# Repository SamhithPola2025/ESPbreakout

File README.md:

# ESPbreakout
## Overview
ESPbreakout is a breakout board for the popular ESP32-s3  chip that includes many breakout pins, compatible with any other ESP32 setup (for the most part), and has programming via USB 2.0.
This board uses the ESP32-S3 SOC, which means that it does not use any of the modules that espressif has already made, and just the bare ESP32-S3 chip.
This board includes pins for progamming, a USB-C port (for programming & power), a screw terminal to convenient wire up a Lithium battery to (3.7v). And you can also utilize the PSRAM that I added externally onto the board. The board includes comprehensive labels for buttons and pins, for ease of use. The cost and materials used to manafacture/make this board are in the BOM.csv file.

## Intent behind making this board:
I made this board to showcase what I already know, and to learn a lot of new things (I can say that this one was accomplished). I also made this board to act as a substitute for the ESP32-S3 devboard that exists, and of course it wont be better than the board made by the actual company, Espressif, but it will be pretty decent and working!

## Pictures

(Pictures of the built version will be added once I get all the components and solder what needs to be soldered, for the most part this is PCBA though.)

| Reference | Quantity | Part                                                   | Unit Price | Extended Price |
| --------- | -------- | ------------------------------------------------------ | ---------- | -------------- |
| PCBA      | 1        | PCBA Estimate                                          | $52.55     | $52.55         |
| B1        | 1        | TinyCircuits BATTERY LITH-ION 3.7V 1AH                 | $9.95      | $9.95          |
| C1        | 1        | Pololu 2PIN F JST PH-STYLE CABLE 12CM                  | $1.47      | $1.47          |
| J1        | 3        | Sullins Connector Solutions CONN HDR 4POS 0.1 GOLD PCB | $0.38      | $1.14          |
| J2        | 1        | Phoenix Contact TERM BLK 2POS SIDE ENTRY 5MM PCB       | $0.78      | $0.78          |
| **Total** |          |                                                        |            | **$71.89**     |

Note: $6.00 of buffer is added for shipping or tariff changes. Any unused buffer will be returned.

## Cart screenshots

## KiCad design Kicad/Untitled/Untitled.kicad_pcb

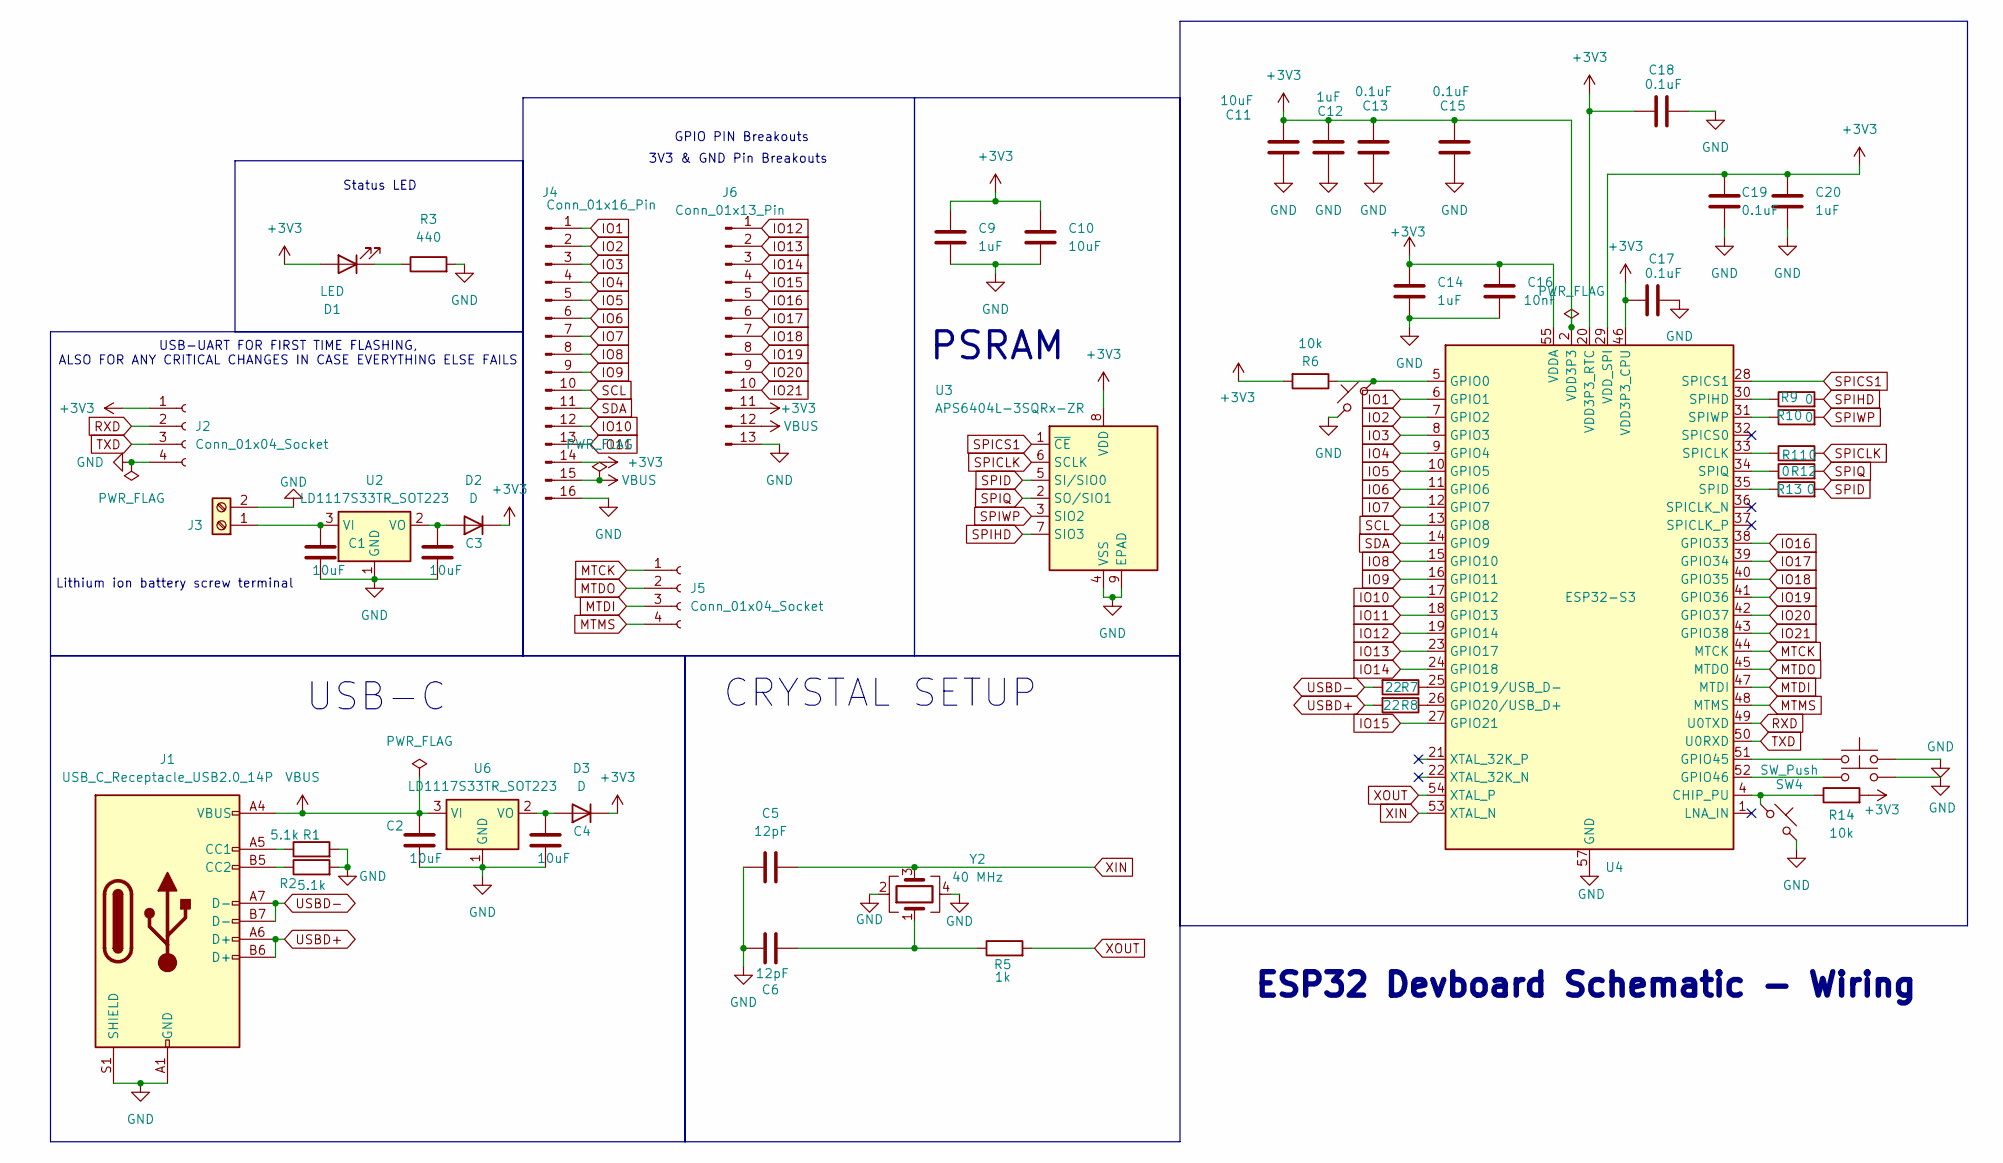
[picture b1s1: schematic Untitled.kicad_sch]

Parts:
C1, C2, C3, C4, C10, C11: 10uF; C_0402_1005Metric
C5, C6: 12pF; C_0402_1005Metric
C9, C12, C14, C20: 1uF; C_0402_1005Metric
C13, C15, C17, C18, C19: 0.1uF; C_0402_1005Metric
C16: 10nF; C_0402_1005Metric
D1: LED; LED_WS2812B-Mini_PLCC4_3.5x3.5mm
D2, D3: D; D_0402_1005Metric
J1: USB_C_Receptacle_USB2.0_14P; HRO_TYPE-C-31-M-12
J2, J5: Conn_01x04_Socket; PinSocket_1x04_P2.54mm_Horizontal
J3: Screw_Terminal_01x02; TerminalBlock_Phoenix_MKDS-1,5-2-5.08_1x02_P5.08mm_Horizont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
J4: Conn_01x16_Pin; PinHeader_1x16_P2.54mm_Vertical
J6: Conn_01x13_Pin; PinHeader_1x13_P2.54mm_Vertical
R1, R2: 5.1k; R_0402_1005Metric
R3: 440; R_0402_1005Metric
R5: 1k; R_0402_1005Metric
R6, R14: 10k; R_0402_1005Metric
R7, R8: 22; R_0402_1005Metric
R9, R10, R11, R12, R13: 0; R_0201_0603Metric
SW1, SW2: SW_Push_45deg; SW_SPST_B3U-1000P
SW3, SW4: SW_Push; SW_SPST_B3U-1000P
U2, U6: LD1117S33TR_SOT223; SOT-223-3_TabPin2
U3: APS6404L-3SQRx-ZR; Winbond_USON-8-1EP_3x2mm_P0.5mm_EP0.2x1.6mm
U4: ESP32-S3; QFN-56-1EP_7x7mm_P0.4mm_EP4x4mm
Y2: 40 MHz; OSC_CX2016DB40000D0FLJCC

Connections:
+3V3: C9.1, C10.1, C11.2, C12.2, C13.2, C14.1, C15.2, C16.1, C17.1, C18.1, C19.1, C20.1, D1.2 (A), D2.1 (K), D3.1 (K), J2.1, J4.14, J6.11, R6.2, R14.2, U3.8 (VDD), U4.2 (VDD3P3), U4.3 (VDD3P3), U4.20 (VDD3P3_RTC), U4.29 (VDD_SPI), U4.46 (VDD3P3_CPU), U4.55 (VDDA), U4.56 (VDDA)
GND: C1.2, C2.2, C3.2, C4.2, C5.1, C6.1, C9.2, C10.2, C11.1, C12.1, C13.1, C14.2, C15.1, C16.2, C17.2, C18.2, C19.2, C20.2, J1.A1 (GND), J1.A12 (GND), J1.B1 (GND), J1.B12 (GND), J1.S1 (SHIELD), J2.4, J3.2, J4.16, J6.13, R1.2, R2.2, R3.2, SW1.1, SW2.2, SW3.2, SW4.2, U2.1 (GND), U3.4 (VSS), U3.9 (EPAD), U4.57 (GND), U6.1 (GND), Y2.2, Y2.4; also elsewhere on the board
IO1: J4.1, U4.6 (GPIO1)
IO2: J4.2, U4.7 (GPIO2)
IO3: J4.3, U4.8 (GPIO3)
IO4: J4.4, U4.9 (GPIO4)
IO5: J4.5, U4.10 (GPIO5)
IO6: J4.6, U4.11 (GPIO6)
IO7: J4.7, U4.12 (GPIO7)
IO8: J4.8, U4.15 (GPIO10)
IO9: J4.9, U4.16 (GPIO11)
IO10: J4.12, U4.17 (GPIO12)
IO11: J4.13, U4.18 (GPIO13)
IO12: J6.1, U4.19 (GPIO14)
IO13: J6.2, U4.23 (GPIO17)
IO14: J6.3, U4.24 (GPIO18)
IO15: J6.4, U4.27 (GPIO21)
IO16: J6.5, U4.38 (GPIO33)
IO17: J6.6, U4.39 (GPIO34)
IO18: J6.7, U4.40 (GPIO35)
IO19: J6.8, U4.41 (GPIO36)
IO20: J6.9, U4.42 (GPIO37)
IO21: J6.10, U4.43 (GPIO38)
MTCK: J5.1, U4.44 (MTCK)
MTDI: J5.3, U4.47 (MTDI)
MTDO: J5.2, U4.45 (MTDO)
MTMS: J5.4, U4.48 (MTMS)
unnamed: C6.2, R5.1, Y2.1
unnamed: D1.1 (K), R3.1
unnamed 29: C3.1, D2.2 (A), U2.2 (VO); also elsewhere on the board
unnamed: C4.1, D3.2 (A), U6.2 (VO)
unnamed: J1.A5 (CC1), R1.1
unnamed: J1.B5 (CC2), R2.1
unnamed 33: C1.1, J3.1, U2.3 (VI); also elsewhere on the board
unnamed: R14.1, SW2.1, U4.4 (CHIP_PU)
unnamed: R6.1, SW1.2, U4.5 (GPIO0)
unnamed: R7.1, U4.25 (GPIO19/USB_D-)
unnamed: R8.1, U4.26 (GPIO20/USB_D+)
unnamed: SW3.1, U4.51 (GPIO45)
unnamed: SW4.1, U4.52 (GPIO46)
unnamed: R11.1, U4.33 (SPICLK)
unnamed: R13.1, U4.35 (SPID)
unnamed: R9.1, U4.30 (SPIHD)
unnamed: R12.1, U4.34 (SPIQ)
unnamed: R10.1, U4.31 (SPIWP)
RXD: J2.2, U4.49 (U0TXD)
SCL: J4.10, U4.13 (GPIO8)
SDA: J4.11, U4.14 (GPIO9)
SPICLK: R11.2, U3.6 (SCLK)
SPICS1: U3.1 (~CE), U4.28 (SPICS1)
SPID: R13.2, U3.5 (SI/SIO0)
SPIHD: R9.2, U3.7 (SIO3)
SPIQ: R12.2, U3.2 (SO/SIO1)
SPIWP: R10.2, U3.3 (SIO2)
TXD: J2.3, U4.50 (U0RXD)
USBD+: J1.A6 (D+), J1.B6 (D+), R8.2
USBD-: J1.A7 (D-), J1.B7 (D-), R7.2
VBUS: C2.1, J1.A4 (VBUS), J1.A9 (VBUS), J1.B4 (VBUS), J1.B9 (VBUS), J4.15, J6.12, U6.3 (VI)
XIN: C5.2, U4.53 (XTAL_N), Y2.3
XOUT: R5.2, U4.54 (XTAL_P)

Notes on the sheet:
USB-UART FOR FIRST TIME FLASHING, ALSO FOR ANY CRITICAL CHANGES IN CASE EVERYTHING ELSE FAILS
CRYSTAL SETUP
GPIO PIN Breakouts
Status LED
Lithium ion battery screw terminal
3V3 & GND Pin Breakouts
USB-C
ESP32 Devboard Schematic - Wiring
PSRAM

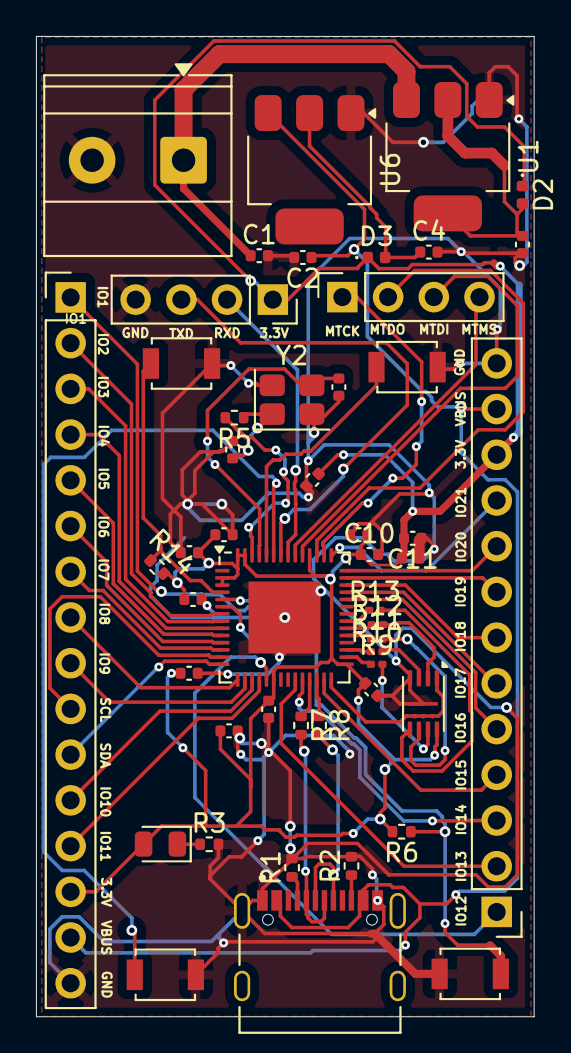
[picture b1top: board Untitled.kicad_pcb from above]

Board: 2 copper layers, 27.7 x 54.5 mm, 49 parts (0 on the bottom side), 60 nets.

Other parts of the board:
U1: NCP1117-3.3_TO252; SOT-223-3_TabPin2

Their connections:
GND: U1.1 (GND); also elsewhere on the board
unnamed 29: U1.2 (VO); also elsewhere on the board
unnamed 33: U1.3 (VI); also elsewhere on the board

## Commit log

2025-10-17 Added basic USBC stuff in schematic, set up some basic pins on the board and started to organize wiring.
2025-10-17 update schematic, more info in journakl
2025-10-18 Add BOM.csv with component details
2025-10-21 journal
2025-10-22 journal entry explains
2025-10-25 journal update
2025-10-29 pcb update
2025-10-31 Fix duplicate entry for J2 in BOM.csv
    Removed duplicate entry for J2 in BOM.
2025-10-31 Fix quantity for J2 in BOM.csv
2025-10-31 Fix formatting of total price in BOM.csv
2025-10-31 Rename PCB Estimate to PCBA Estimate in BOM.csv
2025-10-31 Enhance README with overview and images
    Updated the README to provide a detailed overview of the ESPbreakout board, including its features, intent, and images.
2025-10-31 Update README with component reference and pricing
    Added a reference table for components and pricing.
2025-10-31 Adjust PCBA extended price and total in BOM.csv
    Updated the extended price for PCBA and total cost.
2025-10-31 journal update, pcb update
2025-10-31 sample firmware added
2025-10-31 Update README with cart screenshot
    Added cart screenshot to README.
2025-11-01 Update BOM.csv with new pricing and total calculation
2025-11-01 Revise component pricing and total in README
    Updated component prices and total cost in the README.
